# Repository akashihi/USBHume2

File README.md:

# USBHume2

USB hygrometer and thermometer, based on DTH11/DHT22 sensor.

Once i needed to log humidity change on the premises and it was faster, to build usb based sensor myself, rather then to order ready made device and wait several weeks for delivery

## Getting Started

The solution consists of three parts, combined in a [single repository](https://github.com/akashihi/USBHume2) at github. Those parts are:

* Schematics and board
* Firmware
* Host software

### Prerequisities

For host software you'll need [libusb](http://libusb.org/), [CMake](https://cmake.org/) and, obviously, C compiler. Host software also includes some optional code in Go, so you may need a [Go development kit](https://golang.org/)

Firmware is built on to of STM32 HAL, FreeRTOS and ST's USB library. You will need [Keil uVision 5](http://www.keil.com/) to build or modify it. Pre-built copy of firmware is included into each release.

Schematics and board made with [Eagle](https://cadsoft.io/). PCB is single layer and is compatible with [IDE24S enclosure](http://rcl.lt/index.php?id=2&lang=en&begin=0&acc=show&fid=563&pcode=IDE24S&pmode=&frame=3). Release kit includes PDF with copper, cream and silk masks.

### Making the device

* Make a PCB using your favourite process or order it somewhere.
* Solder USB connector and power supply part (IC1, C3, C4, C5, C7, JP1)
* Plug device into USB and check voltage between JP1 pins, it should be 3.3V
* Solder everything else

#### Partlist

* 1x STM32F042F6P6
* 1x LM1117IMP-3.3
* 2x 10u tantalum capacitors (C5, C7)
* 5x 100n 1206 capacitors (C1, C2, C3, C4, C6)
* 1x 510 0805 resistor (R1)
* 1x 10k 0805 resistor (R2)
* 1x 1k 0805 resistor (R4)
* 1x chip led 0805 (LED3)

### Making the firmware

Install [Keil uVision 5](http://www.keil.com/) and build firmware from directory **fw** using normal procedure.

#### Firmware implementation details

Firmware is built on top of STM32 HAL, FreeRTOS and ST's USB library. In implements custom HID device, that can be only read.

**VID: 0xF055**

**PID: 0xA8D1**

Firmware provides out interface 0 with report id 0x81. Requesting that report will result in getting four bytes:

* humidity value
* error code
* temperature value
* always zero

If error code is not zero, other values shouldn't be trusted. Possible values for error code are:

* 0x01 - sensor doesn't replies to requests.
* 0x02 - sensor confirmed request, but didn't transferred response.
* 0xED - request transferred ok, but CRC check failed.

It is normal to see those errors from time to time (especially after device power-up), but continuous stream of errors mean hardware malfunction.

Humidity and temperature values could contain special codes, like 0xFF or 0xEE, meaning timeout during reading that value. Appearance of such codes is usually accompanied with 0xED value in error code field.

Firmware internally is built using three tasks - one task for blinking RDY led to signal that we are still alive and running. Second thread is requesting measurements from sensor every 60 seconds and third thread is responding to usb read request every 100ms or faster.

#### Firmware flashing

After you built your USBHume2 device and built firmware (or downloaded ready made firmware from the release package), you need to flash the firmware into device.

Device uses SWD interface with three pins on the PCB.

* JP1 - SWDIO
* JP2 - SWDCLK
* JP3 - NRST

Connect those pins to your SWD flasher, optionally connect pins JP4 and JP5 to power-on the device and upload the firmware using your flasher's software.

## Host software

Host software consists of abstraction library and couple of usage examples.

### libusbhume - interface for USB hygrometer USBHume2.

#### Introduction

USBHume2 device is a USB HID class device, so it soesn't requires special drivers. 

Device can only be read and it usually returns relative humidity in percents and  temperature in Celcius degrees or error in case of sensor failure. 

libusbhume is mostly a wrapper over libusb, that hides low level stuff and allows end user to work with high level abstractions. At the moment it doesn't support neither several devices nor device selection and it's functionality is very limited.

libusbhume usage is quite easy:
* Open device
* Request measurements one or more times
* Close device 
    
#### Getting and installing
   
The libusbhume source code is hosted on [github](https://github.com/akashihi/USBHume2"), as a partof USBHume2 repository, so you can download the source code using wget or other download tool:
     
* https://github.com/akashihi/USBHume2/tarball/master (tar.gz format)
* https://github.com/akashihi/USBHume2/zipball/master (or zip format)
     
You could also clone the repository and check some unstable code:
     
```
git clone git://github.com/akashihi/USBHume2.git
```
     
The 'master' branch is always pointing to the latest stable release and the 'next' branch is a unstable development branch.
     
Host part of USBHume2 (libusbhume and some examples) is in /host directory.  To build libusbhume you'll need:
     
* [Recent CMake (required)](http://www.cmake.org/)
* [libusb (required)](http://libusb.org/)
* [Doxygen (optional, only for documentation processing)](http://www.doxygen.org/)
     
After getting this stuff up and running, select a directory for building and issue the following commands:
     
```
cmake /path/to/the/USBHume2/sources/host        
make
make test
make doc
make install
```
     
The CMake is using a [out-of-source](http://www.cmake.org/Wiki/CMake_FAQ#Out-of-source_build_trees) build approach, so it is recommended to create a temporary build directory somewhere and remove it after installation.
     
The generated documentation will be put into the *build*/doc directory. The documentation is NOT installed by ```make install``` command, so you have to copy it manually, if you really need it.
     
#### Usage
     
Open device, query device, close device.
     
```c
struct usbhumeDevice* uh = usbhumeOpen();
struct usbhumeData *reply = usbhumeRequest(uh);
free(reply);
usbhumeClose(uh);
```

struct usbhumeDevice is a opaque object, whose lifecycle is managed by libusb. On the other hand struct usbhumeData should be freed by your app.

### usbhumereq - measurement request utility

usbhumereq, located in host/src/usbhume queries device for current measurement and prints it to stdout. It's main purpose is to show how to use libusbhume and check that device is working. You need to provide that binary with capabilities to work with usb bus and detach devices from kernel drivers.

```
sudo ./usbhumereq
RH 44%, T 21C
```

### usbhume2graphite - graphite metrics gatherintg utility

usbhume2graphite is a tool to periodically poll device and send humidity/temperature data to the [Graphite](https://graphiteapp.org/).

This tool is built in Go language and requires Go development kit to be installed.

#### How to build usbhume2graphite

* Install [Go](https://golang.org/)
* Install graphite package for Go ```go get -u github.com/marpaia/graphite-golang```
* Build libusbhume, as described above
* Copy libusbhume binary AND header file into usbhume2graphite folder
* Build the binary ```go build```

#### How to use usbhume2graphite

```
sudo ./usbhume2grpahite -period 60 -metrics-host 127.0.0.1 -metrics-port 2003 -metrics-prefix usbhume2
```

Values, shown above, are default values for configuration options.

* *period* defines poll period in seconds. Don't forget, device makes measurements every 60 seconds, so there is no need to poll it more frequently.
* *metrics-host* address of Graphite metrics collector
* *metrics-port* port of Graphite metrics collector
* *metrics-prefix* usbhume2graphite posts two metrics: T and RH and those metrics will be prefixed with *metrics-prefix*.

#Limitations

Measurement limitations are defined by used sensor. For DHT11 it would be:

* RH range: 20%-95%
* RH measurement error: 5%
* Temperature range: 0-50 Celsius degrees
* Temperature measurement error: 2%

As for device itself, it have two limitations:

* Sensor is polled once per 60 seconds. I discovered, that faster polling could heat-up the sensor itself and add more error to measurements. Anyway, under normal conditions temperature and humidity are not changing very fast.
* You can't attach several devices to a single host and library doesn't supports it. As device problem could be fixed by changing serial no in the firmware and keeping it unique over several devices, library would require more changes. May be sometime i'll fix it.

#Bugs

Lots.

# Authors

* **Denis Chapligin** - *Initial work* - https://github.com/akashihi

# License

This project is licensed under the GPLv3 License - see the [LICENSE](LICENSE) file for details.

Firmware code includes parts of FreeRTOS and ST libraries, licensed undet MIT license.

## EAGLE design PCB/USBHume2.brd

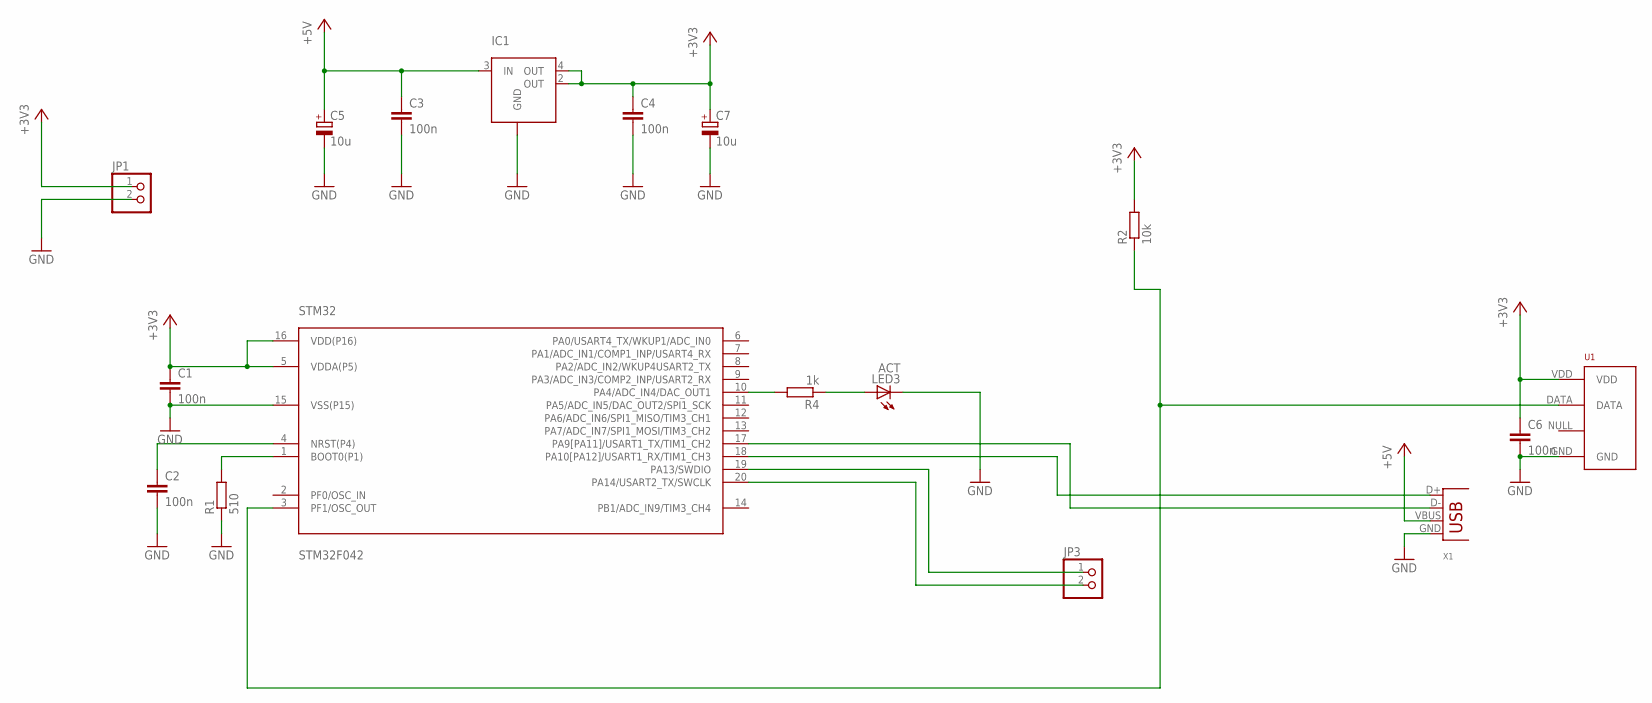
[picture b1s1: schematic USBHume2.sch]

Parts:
C1, C2, C3, C4, C6: 100n; C1206K
C5, C7: 10u; C/6032-28R
IC1: LM1117MP-3.3; SOT223
JP1, JP3: PINHD-1X2; 1X02
LED3: ACT; CHIPLED_0805
R1: 510; M0805
R2: 10k; M0805
R4: 1k; M0805
STM32: STM32F042; TSSOP20
U1: RHT03_DHT-22_AM2302WIRED; AM2302
X1: USB-A-H

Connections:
+3V3: C1.1, C4.1, C6.1, C7.+, IC1.2 (OUT), IC1.4 (OUT), JP1.1, R2.2, STM32.5 (VDDA(P5)), STM32.16 (VDD(P16)), U1.VDD
+5V: C3.1, C5.+, IC1.3 (IN), X1.VBUS
GND: C1.2, C2.2, C3.2, C4.2, C5.-, C6.2, C7.-, IC1.1 (GND), JP1.2, LED3.C, R1.1, STM32.15 (VSS(P15)), U1.GND, X1.GND
unnamed: R2.1, STM32.3 (PF1/OSC_OUT), U1.DATA
unnamed: R4.2, STM32.10 (PA4/ADC_IN4/DAC_OUT1)
unnamed: STM32.17 (PA9[PA11]/USART1_TX/TIM1_CH2), X1.D-
unnamed: STM32.18 (PA10[PA12]/USART1_RX/TIM1_CH3), X1.D+
unnamed: R1.2, STM32.1 (BOOT0(P1))
unnamed: JP3.1, STM32.19 (PA13/SWDIO)
unnamed: JP3.2, STM32.20 (PA14/USART2_TX/SWCLK)
unnamed: LED3.A, R4.1
unnamed: C2.1, STM32.4 (NRST(P4))

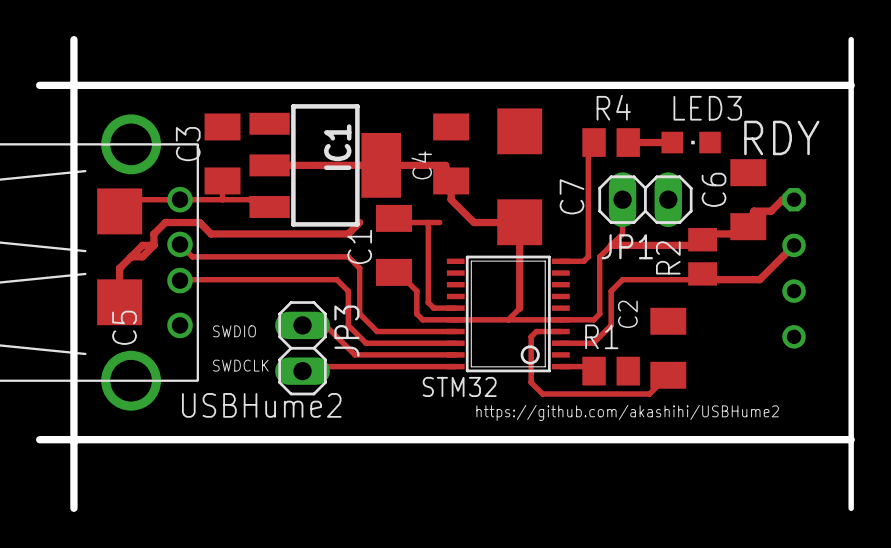
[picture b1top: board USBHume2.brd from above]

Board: 2 copper layers, 45.1 x 26.0 mm, 17 parts (1 on the bottom side), 12 nets.

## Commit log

2016-08-07 Added .gitignore
2016-08-08 Schematics and Board added.
2016-08-08 Layout change
2016-08-08 Added host library and reading programm.
2016-08-08 Added doxygen docs.
2016-08-08 Typos fixed.
2016-08-08 Added graphite gateway example written in go.
2016-08-08 Fixed cmake definition.
2016-08-09 Added hal libraries and freertos
2016-08-09 Updated gitignore
2016-08-09 Added Keil project files.
2016-08-09 Firmware code added.
2016-08-09 Added documentation
2016-08-09 Typos fixed
2016-08-14 Added pin remapping for TSSOP20 package
2016-08-15 Massive libraries clean-up
2016-08-15 Disabled FreeRTOS tracing
2016-08-15 DHT handling moved to separate file.
2016-08-15 Timer events switched to semaphores instead of queues
2016-08-15 USB data sending period decreased to 10ms
2016-08-15 USB code cleanup
2016-08-15 Fixed queue type
2016-08-15 Tuned HID descriptot
2016-08-17 Parts sizes fixed. Board errors fixed.
2016-08-30 Fixed memory leak in usb access.
2016-08-31 Graphite connection should be closed in cycle.
2016-09-13 Board simplification
2016-09-26 Programming pins grouped
2016-09-26 Documentation updated
